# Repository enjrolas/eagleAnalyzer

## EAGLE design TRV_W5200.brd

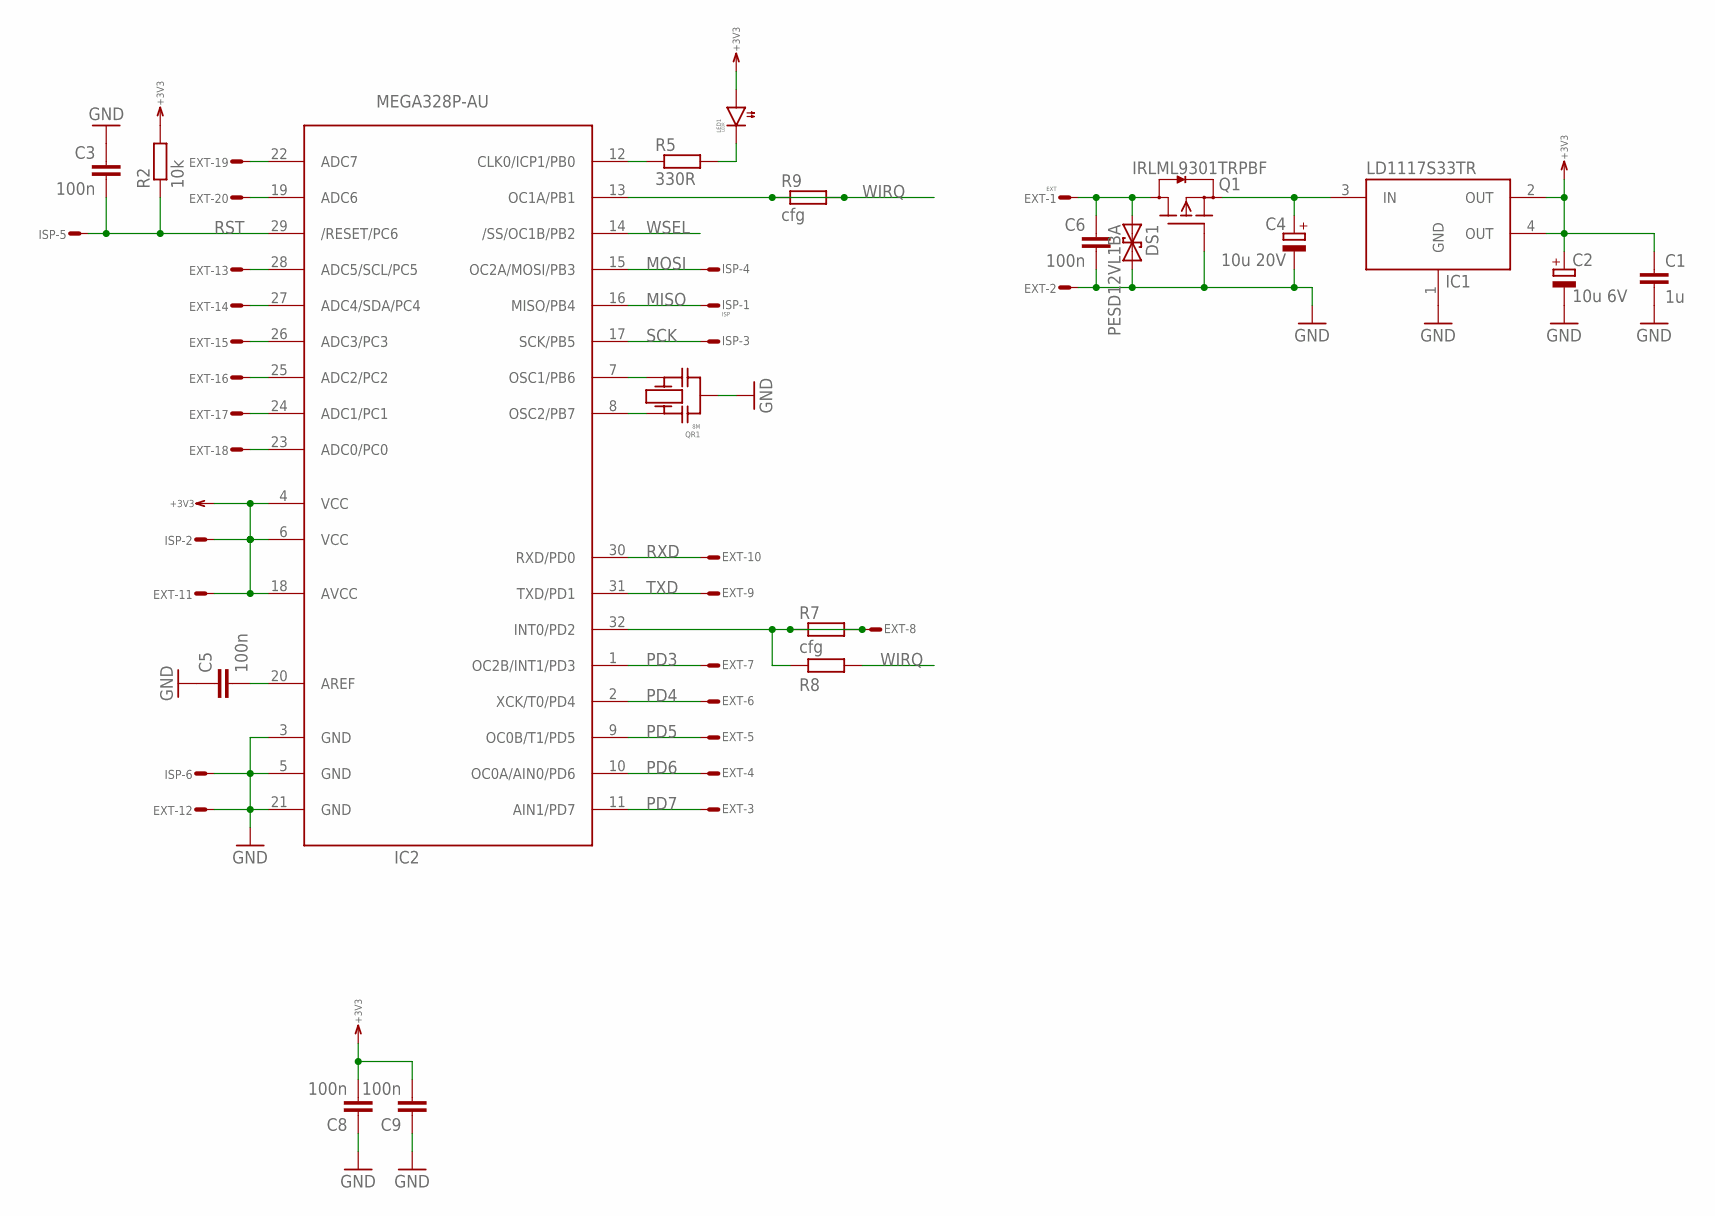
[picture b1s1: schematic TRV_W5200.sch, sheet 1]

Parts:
C1: 1u; 0603
C2: 10u 6V; SMC_A
C3, C5, C6, C8, C9: 100n; 0603
C4: 10u 20V; SMC_B
DS1: PESD12VL1BA; SOD323
EXT: EXT; ML20S
IC1: LD1117S33TR; SOT223
IC2: MEGA328P-AU; TQFP32-08
ISP: ISP; ML6S
LED1: LEDR; T1-3/4
Q1: IRLML9301TRPBF; SOT23
QR1: 8M; CSTCE
R2: 10k; 0603
R5: 330R; 0603
R7, R8, R9: cfg; 0402

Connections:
+3V3: C1.1, C2.+, C8.2, C9.2, EXT.11, IC1.2 (OUT), IC1.4 (OUT), IC2.4 (VCC), IC2.6 (VCC), IC2.18 (AVCC), ISP.2, LED1.A, R2.2; also elsewhere on the board
GND: C1.2, C2.-, C3.1, C4.-, C5.1, C6.2, C8.1, C9.1, DS1.C (2), EXT.2, EXT.12, IC1.1 (GND), IC2.3 (GND), IC2.5 (GND), IC2.21 (GND), ISP.6, Q1.1 (G), QR1.G (M); also elsewhere on the board
MISO: IC2.16 (MISO/PB4), ISP.1; also elsewhere on the board
MOSI: IC2.15 (OC2A/MOSI/PB3), ISP.4; also elsewhere on the board
unnamed: C6.1, DS1.A (1), EXT.1, Q1.3 (D)
unnamed: EXT.19, IC2.22 (ADC7)
unnamed: C4.+, IC1.3 (IN), Q1.2 (S)
unnamed: C5.2, IC2.20 (AREF)
unnamed: IC2.8 (OSC2/PB7), QR1.A (1)
unnamed: IC2.7 (OSC1/PB6), QR1.B (2)
unnamed: IC2.12 (CLK0/ICP1/PB0), R5.1
unnamed: EXT.8, IC2.32 (INT0/PD2), R7.1, R7.2, R8.1
unnamed: EXT.20, IC2.19 (ADC6)
unnamed: LED1.C, R5.2
PC0: EXT.18, IC2.23 (ADC0/PC0)
PC1: EXT.17, IC2.24 (ADC1/PC1)
PC2: EXT.16, IC2.25 (ADC2/PC2)
PC3: EXT.15, IC2.26 (ADC3/PC3)
PC4: EXT.14, IC2.27 (ADC4/SDA/PC4)
PC5: EXT.13, IC2.28 (ADC5/SCL/PC5)
PD3: EXT.7, IC2.1 (OC2B/INT1/PD3)
PD4: EXT.6, IC2.2 (XCK/T0/PD4)
PD5: EXT.5, IC2.9 (OC0B/T1/PD5)
PD6: EXT.4, IC2.10 (OC0A/AIN0/PD6)
PD7: EXT.3, IC2.11 (AIN1/PD7)
RST: C3.2, IC2.29 (/RESET/PC6), ISP.5, R2.1
RXD: EXT.10, IC2.30 (RXD/PD0)
SCK: IC2.17 (SCK/PB5), ISP.3; also elsewhere on the board
TXD: EXT.9, IC2.31 (TXD/PD1)
WIRQ: IC2.13 (OC1A/PB1), R8.2, R9.1, R9.2; also elsewhere on the board
WSEL: IC2.14 (/SS/OC1B/PB2); also elsewhere on the board

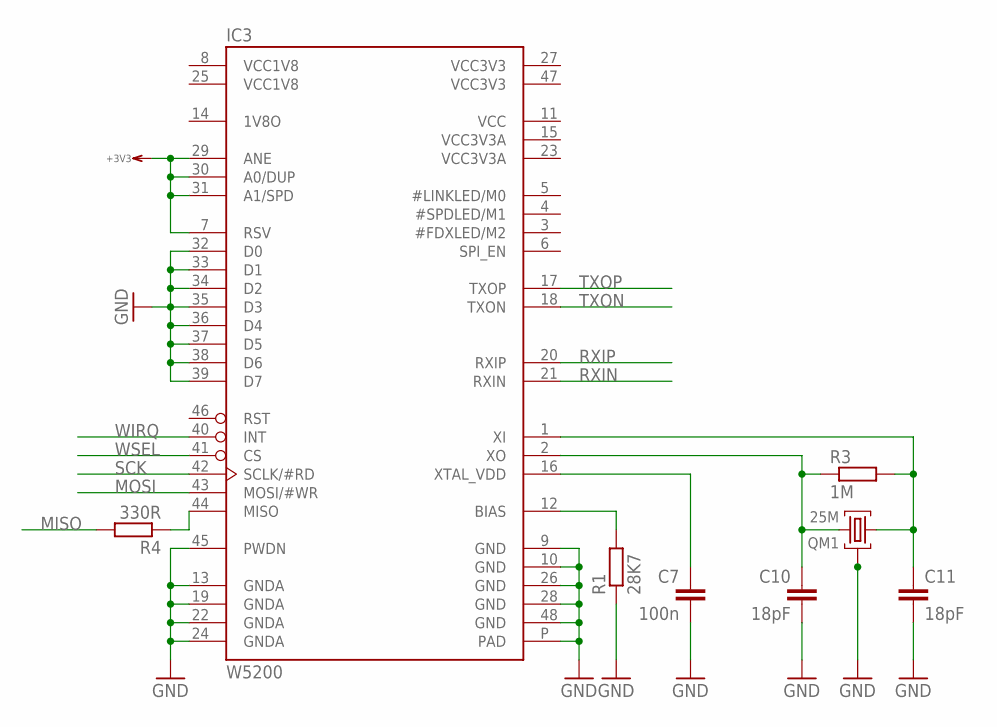
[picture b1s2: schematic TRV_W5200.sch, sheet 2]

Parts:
C7: 100n; 0603
C10, C11: 18pF; 0603
IC3: W5200; QFN48
QM1: 25M; SMD_4P_3.2X2.5
R1: 28K7; 0603
R3: 1M; 0603
R4: 330R; 0603

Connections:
+3V3: IC3.7 (RSV), IC3.29 (ANE), IC3.30 (A0/DUP), IC3.31 (A1/SPD); also elsewhere on the board
GND: C7.2, C10.2, C11.2, IC3.9 (GND), IC3.10 (GND), IC3.13 (GNDA), IC3.19 (GNDA), IC3.22 (GNDA), IC3.24 (GNDA), IC3.26 (GND), IC3.28 (GND), IC3.32 (D0), IC3.33 (D1), IC3.34 (D2), IC3.35 (D3), IC3.36 (D4), IC3.37 (D5), IC3.38 (D6), IC3.39 (D7), IC3.45 (PWDN), IC3.48 (GND), IC3.P (PAD), QM1.2 (M1), QM1.4 (M2), R1.1; also elsewhere on the board
MISO: R4.2; also elsewhere on the board
MOSI: IC3.43 (MOSI/#WR); also elsewhere on the board
unnamed: IC3.12 (BIAS), R1.2
unnamed: C7.1, IC3.16 (XTAL_VDD)
unnamed: C10.1, IC3.2 (XO), QM1.3 (2), R3.1
unnamed: C11.1, IC3.1 (XI), QM1.1, R3.2
unnamed: IC3.44 (MISO), R4.1
RXIN: IC3.21 (RXIN)
RXIP: IC3.20 (RXIP)
SCK: IC3.42 (SCLK/#RD); also elsewhere on the board
TXON: IC3.18 (TXON)
TXOP: IC3.17 (TXOP)
WIRQ: IC3.40 (INT); also elsewhere on the board
WSEL: IC3.41 (CS); also elsewhere on the board

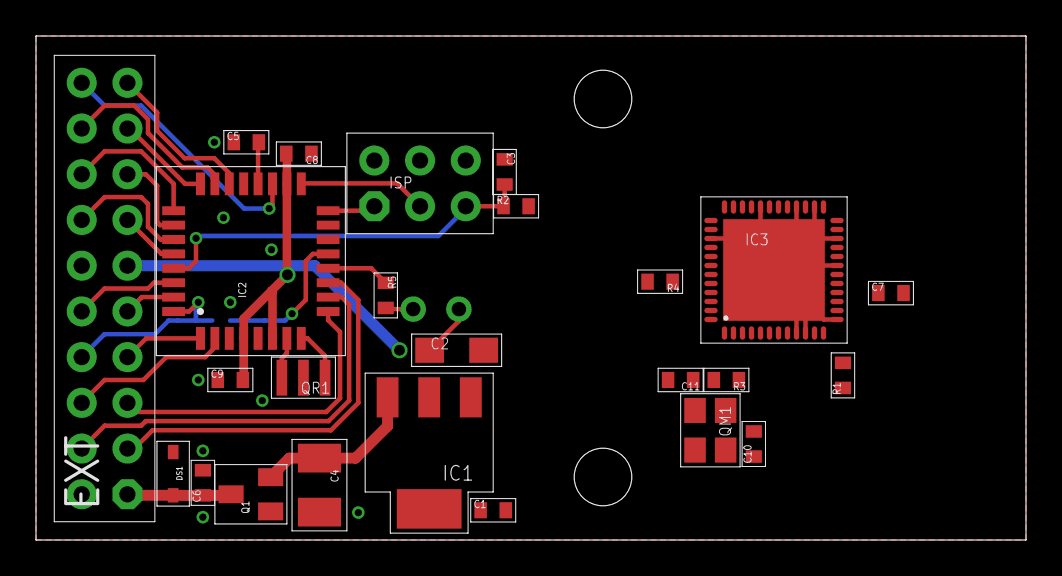
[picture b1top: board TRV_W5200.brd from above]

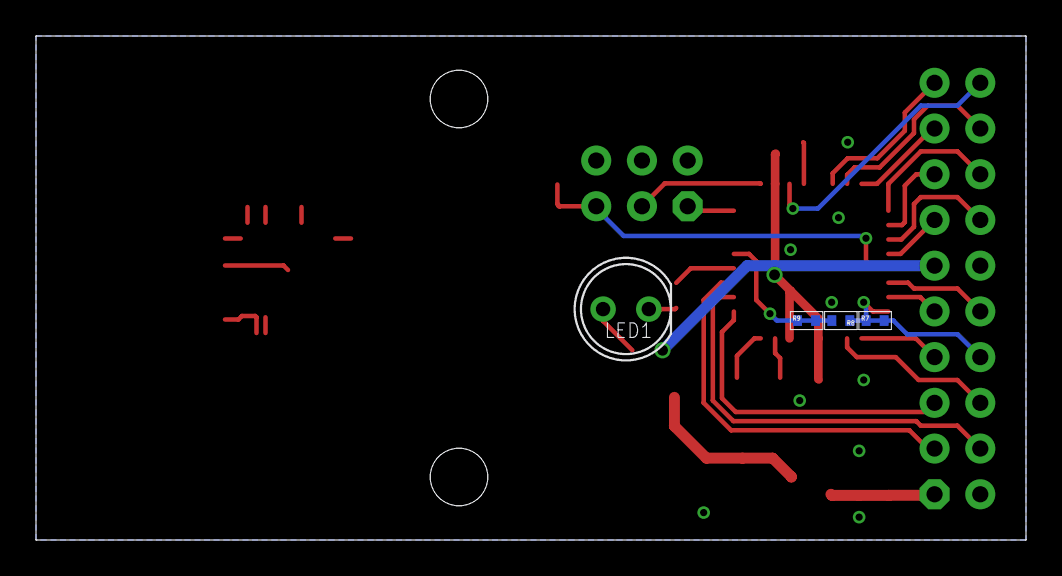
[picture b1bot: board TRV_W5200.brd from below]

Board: 2 copper layers, 55.0 x 28.0 mm, 29 parts (4 on the bottom side), 36 nets.

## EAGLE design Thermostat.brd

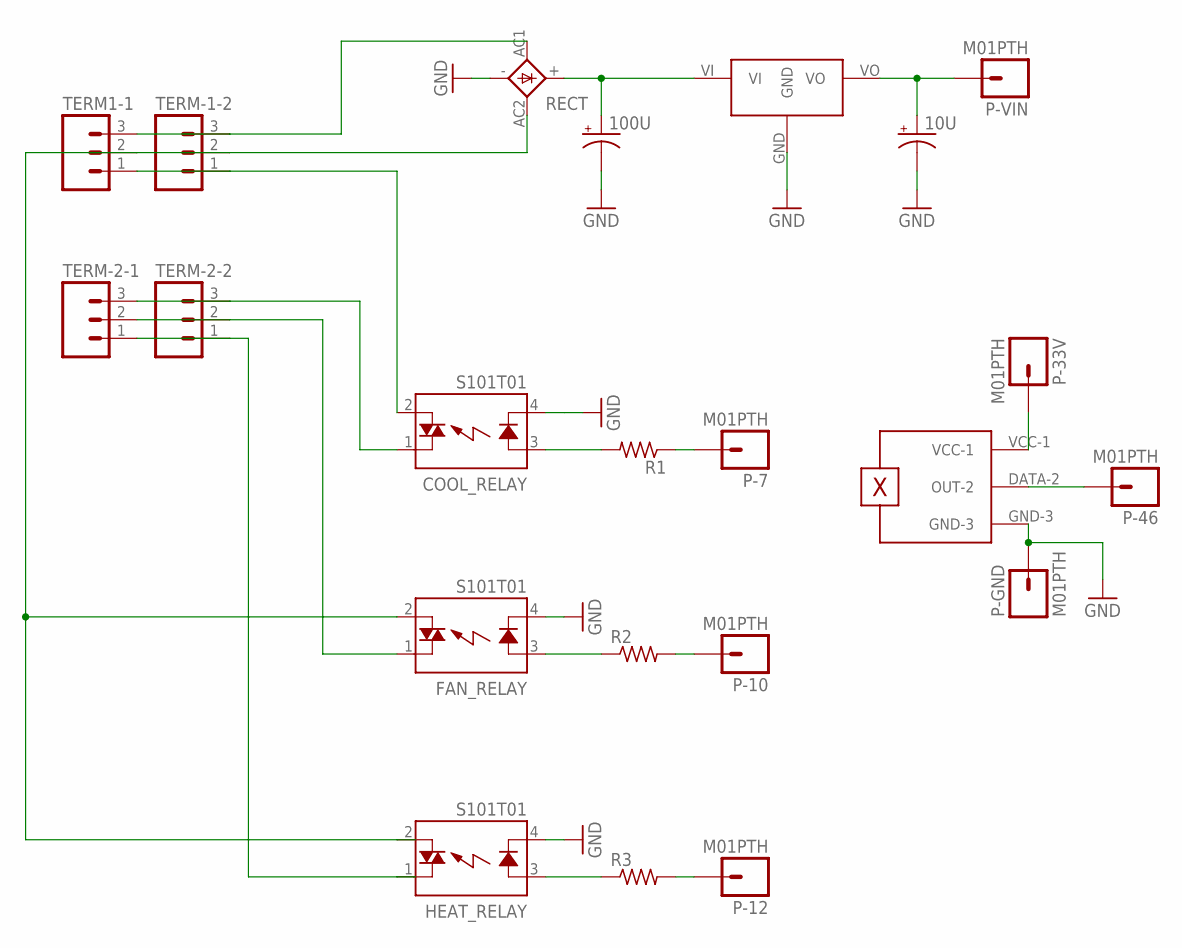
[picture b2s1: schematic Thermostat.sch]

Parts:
10U: CAP_POLPTH2; CPOL-RADIAL-10UF-25V
100U: CAP_POLPTH1; CPOL-RADIAL-100UF-25V
COOL_RELAY: S101T01; S102T0X
FAN_RELAY: S101T01; S102T0X
HEAT_RELAY: S101T01; S102T0X
P-7, P-10, P-12, P-33V, P-46: M01PTH; 1X01
P-GND: M01PTH; 1X01
P-VIN: M01PTH; 1X01
R1, R2, R3: R-US_0204/2V; 0204V
RECT: GBU4; GBU4S
TERM1-1: M031X03_NO_SILK; 1X03_NO_SILK
TERM-1-2, TERM-2-1, TERM-2-2: M031X03_NO_SILK; 1X03_NO_SILK
U$1: TMP36
U$2: V715W-500R; SWITCHINGREGULATOR

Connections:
GND: 10U.2 (-), 100U.2 (-), COOL_RELAY.4 (K), FAN_RELAY.4 (K), HEAT_RELAY.4 (K), P-GND.1, RECT.-, U$1.GND-3, U$2.GND
unnamed: COOL_RELAY.2 (DS2), TERM1-1.1, TERM-1-2.1
unnamed: HEAT_RELAY.3 (A), R3.1
unnamed: RECT.AC1 (AC2), TERM1-1.3, TERM-1-2.3
unnamed: P-7.1, R1.1
unnamed: P-46.1, U$1.DATA-2 (OUT-2)
unnamed: FAN_RELAY.3 (A), R2.1
unnamed: P-10.1, R2.2
unnamed: P-12.1, R3.2
unnamed: COOL_RELAY.3 (A), R1.2
unnamed: 10U.1 (+), P-VIN.1, U$2.VO
unnamed: P-33V.1, U$1.VCC-1
unnamed: 100U.1 (+), RECT.+, U$2.VI
unnamed: HEAT_RELAY.1 (DS1), TERM-2-1.1, TERM-2-2.1
unnamed: COOL_RELAY.1 (DS1), TERM-2-1.3, TERM-2-2.3
unnamed: FAN_RELAY.1 (DS1), TERM-2-1.2, TERM-2-2.2
P2: FAN_RELAY.2 (DS2), HEAT_RELAY.2 (DS2), RECT.AC2 (AC1), TERM1-1.2, TERM-1-2.2

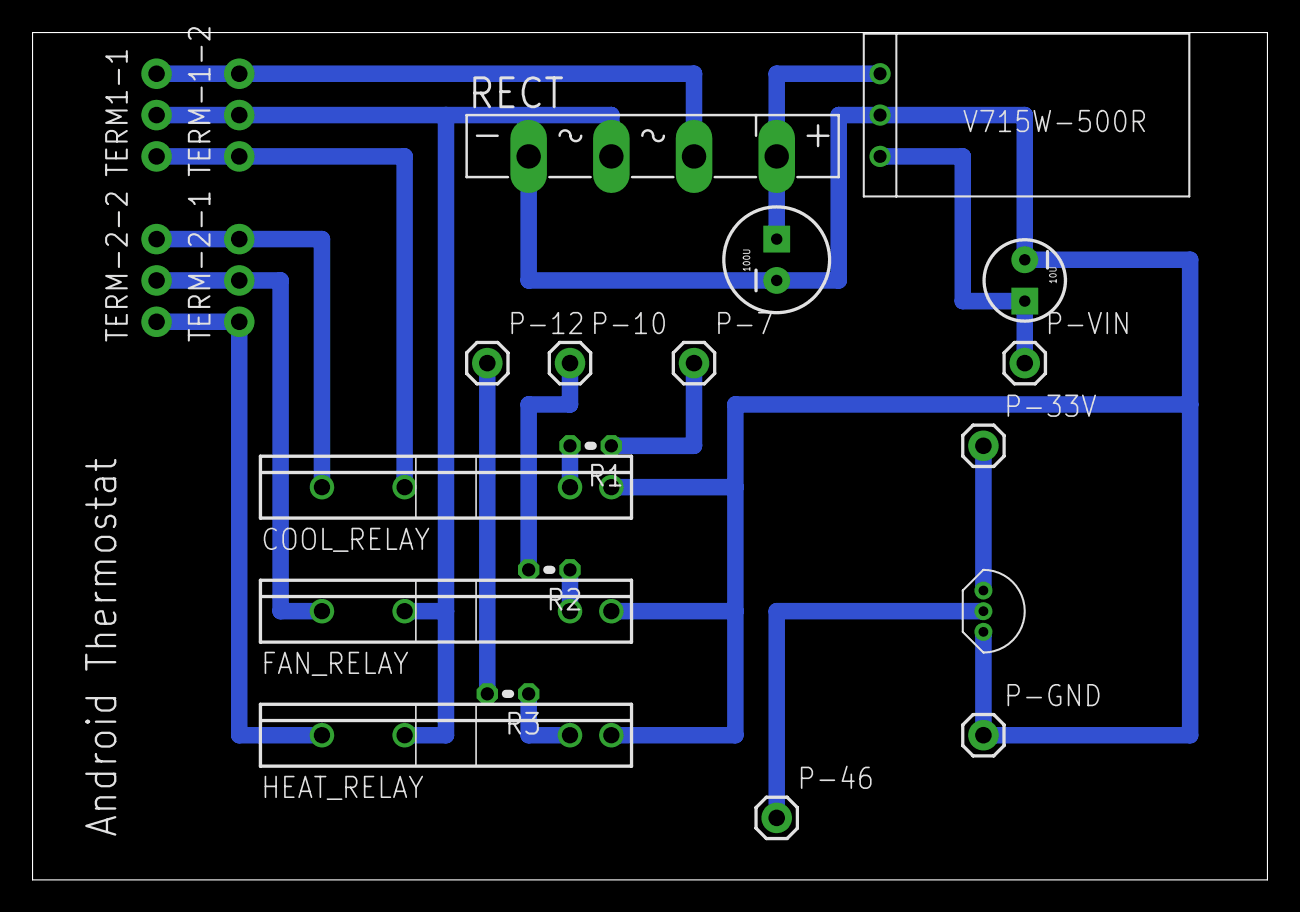
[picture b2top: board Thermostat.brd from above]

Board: 2 copper layers, 75.9 x 52.1 mm, 22 parts (0 on the bottom side), 17 nets.

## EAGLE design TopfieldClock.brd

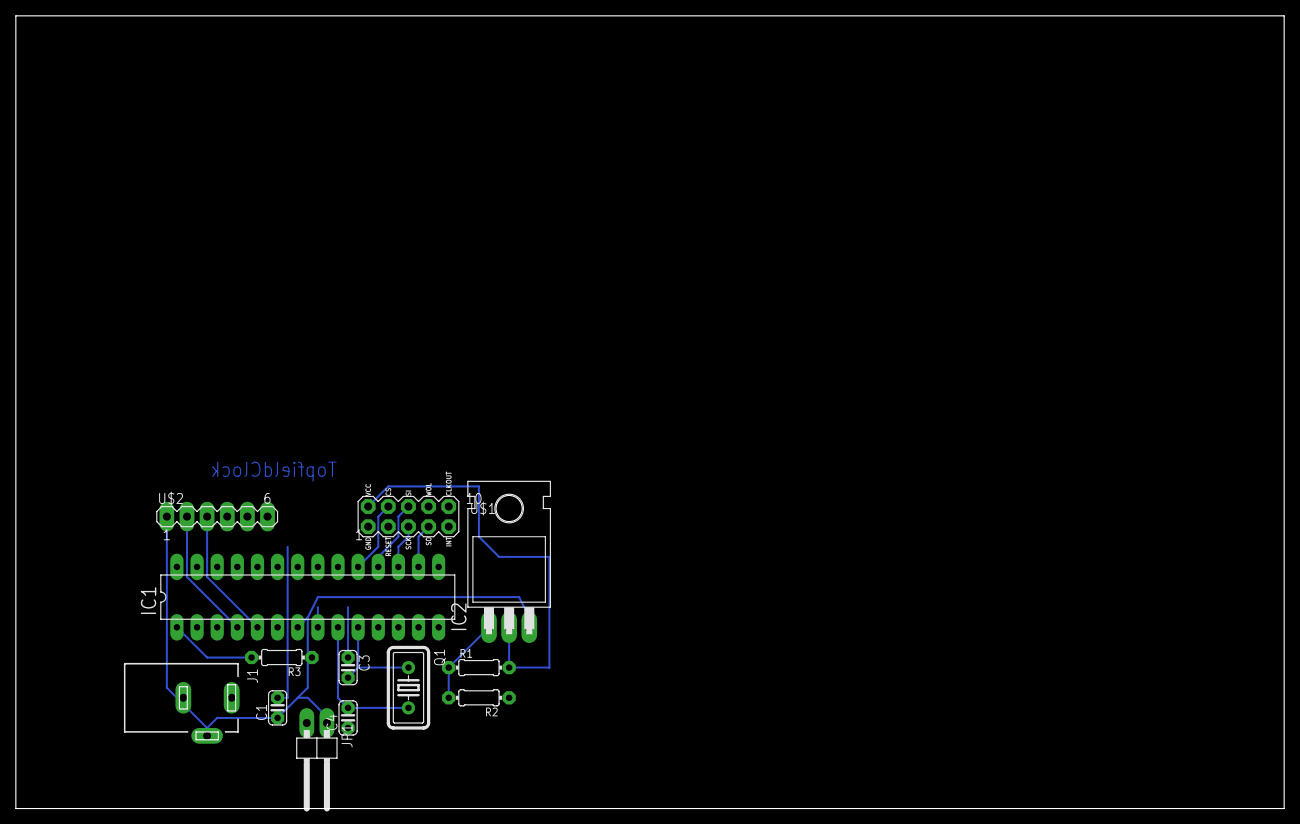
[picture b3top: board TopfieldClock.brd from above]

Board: 2 copper layers, 160.0 x 100.0 mm, 13 parts (0 on the bottom side), 13 nets.

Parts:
C1: 1u; C025-024X044
C3, C4: 22p; C025-024X044
IC1: ATMEGA168-PU; DIL28-3
IC2: 317T; TO220H
J1: DCJ0202
JP1: 1X02/90
Q1: 16M; HC18U-V
R1: 390; 0204/7
R2: 670; 0204/7
R3: 5k; 0204/7
U$1: ENC28J60MODULEENC28J60MODULECONN; ENC28J60MODULECONN
U$2: TF5000FRONTPANEL; MA06-1

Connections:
+3V3: IC2.2, R1.2, U$1.2
GND: C1.2, C3.1, C4.1, IC1.8, J1.1, JP1.2, R2.1, U$1.1, U$2.4
unnamed: IC1.4, U$2.2
unnamed: IC1.19, U$1.4
unnamed: IC1.17, U$1.5
unnamed: IC1.18, U$1.6
unnamed: IC1.5, U$2.3
unnamed: IC1.16, U$1.7
unnamed: IC2.1, R1.1, R2.2
unnamed: IC1.1, R3.2
VCC: C1.1, IC1.7, IC2.3, J1.2, J1.3, JP1.1, R3.1, U$2.1
XTAL1: C4.2, IC1.9, Q1.2
XTAL2: C3.2, IC1.10, Q1.1

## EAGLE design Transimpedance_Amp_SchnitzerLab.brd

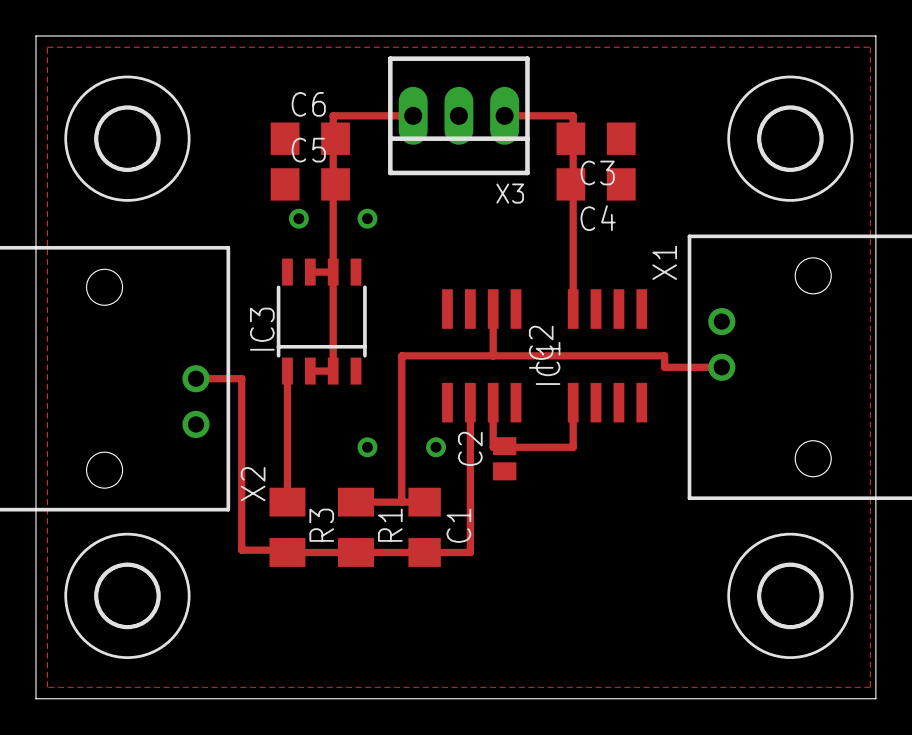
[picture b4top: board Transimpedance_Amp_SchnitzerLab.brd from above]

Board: 2 copper layers, 46.7 x 36.8 mm, 18 parts (0 on the bottom side), 7 nets.

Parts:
C1: C1206
C2: 100nf; C0504
C3, C6: 6.8uf; C1206
C4, C5: 2.2uf; C1206
IC1: SO08
IC2, IC3: SOIC8
R1, R3: M1206
U$1, U$2, U$3, U$4: 3,3
X1, X2: AMP_227161
X3: 22-23-2031

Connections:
+15V: C3.2, C4.2, IC1.8, X3.1
-5V: IC3.1, R3.1
-15V: C5.2, C6.2, IC3.2, IC3.3, IC3.6, IC3.7, X3.3
GND: C2.1, C3.1, C4.1, C5.1, C6.1, IC1.2, IC1.3, IC1.6, IC1.7, IC2.3, IC2.4, IC3.5, X1.2, X2.2, X3.2
unnamed: C1.1, IC2.2, R1.1, X1.1
unnamed: C1.2, IC2.6, R1.2, R3.2, X2.1
V+: C2.2, IC1.1, IC2.7

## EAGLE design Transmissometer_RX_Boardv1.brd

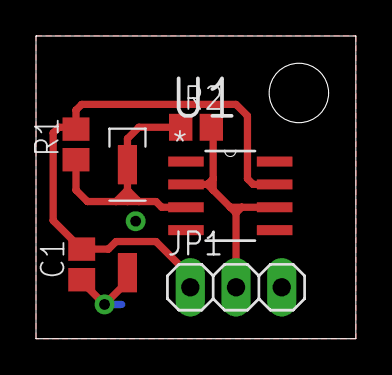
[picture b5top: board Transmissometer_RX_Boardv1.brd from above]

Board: 2 copper layers, 17.8 x 16.8 mm, 7 parts (0 on the bottom side), 4 nets.

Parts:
C1: 0.1u; C0805
JP1: 1X03
R1: 1K; R0805
R2: NP; R0805
U1: AD8628ARZ-REEL7; SOIC127P600X175-8N
U$1: TEMPT1020
U$2: STAND-OFF

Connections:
+5V: C1.2, JP1.1, R1.2, U1.7
GND: C1.1, JP1.3, U1.4, U$1.P$1
unnamed: R1.1, R2.1, U1.3, U$1.P$2
OUT: JP1.2, R2.2, U1.2, U1.6

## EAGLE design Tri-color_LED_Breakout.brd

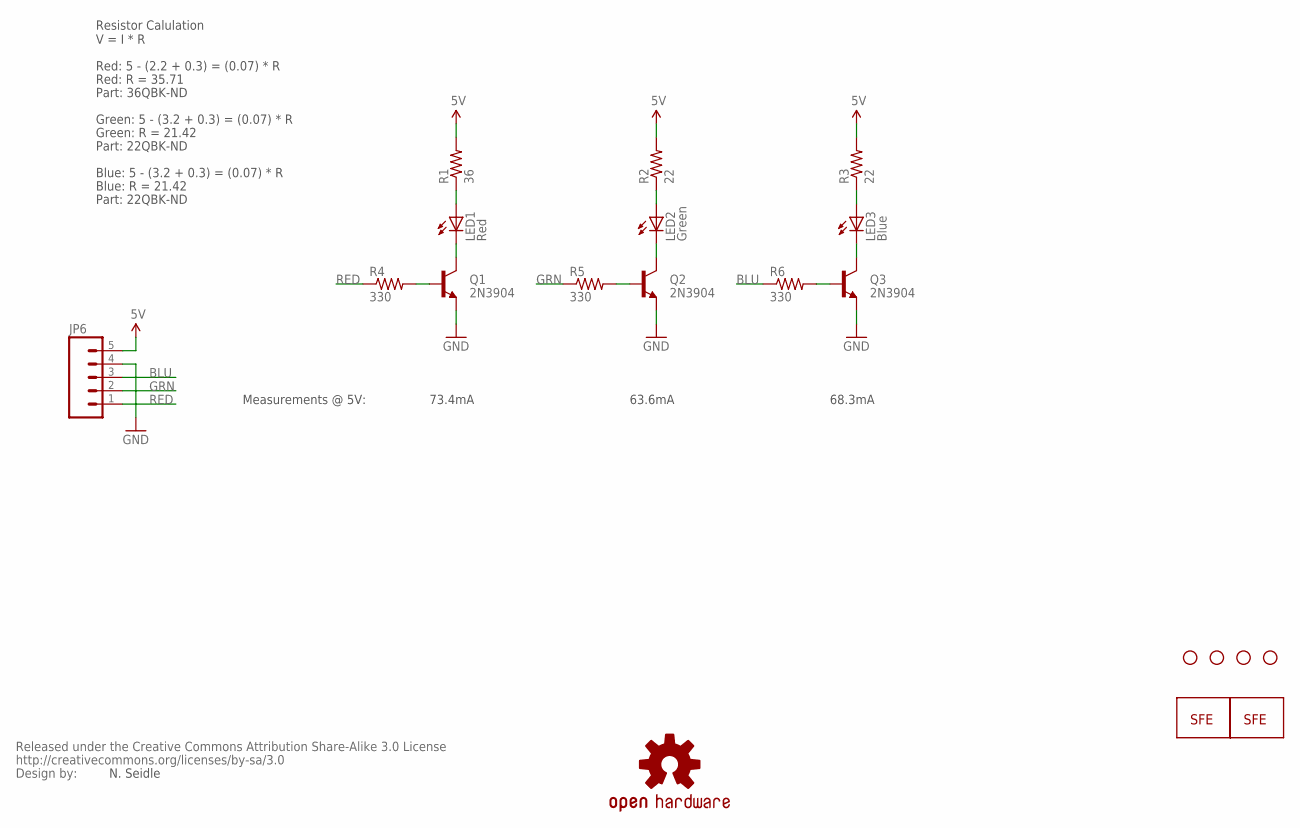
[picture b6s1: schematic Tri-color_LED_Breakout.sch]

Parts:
JP1, JP2, JP3, JP4: STAND-OFF
JP5, JP7: LOGO-SFESK; SFE-LOGO-FLAME
JP6: M05PTH; 1X05
LED1: Red; LED10MM
LED2: Green; LED10MM
LED3: Blue; LED10MM
Q1, Q2, Q3: 2N3904; TO-92
R1: 36; AXIAL-0.4
R2, R3: 22; AXIAL-0.4
R4, R5, R6: 330; AXIAL-0.3
U$1: CREATIVE_COMMONS
U$6: OSHW-LOGOS; OSHW-LOGO-S

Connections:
5V: JP6.5, R1.P$2 (2), R2.P$2 (2), R3.P$2 (2)
BLU: JP6.3, R6.P$1 (1)
GND: JP6.4, Q1.1 (E), Q2.1 (E), Q3.1 (E)
GRN: JP6.2, R5.P$1 (1)
unnamed: LED2.A, R2.P$1 (1)
unnamed: LED3.A, R3.P$1 (1)
unnamed: LED1.A, R1.P$1 (1)
unnamed: LED1.C, Q1.3 (C)
unnamed: LED2.C, Q2.3 (C)
unnamed: LED3.C, Q3.3 (C)
unnamed: Q1.2 (B), R4.P$2 (2)
unnamed: Q2.2 (B), R5.P$2 (2)
unnamed: Q3.2 (B), R6.P$2 (2)
RED: JP6.1, R4.P$1 (1)

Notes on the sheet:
N. Seidle
Resistor Calulation V = I * R
Red: 5 - (2.2 + 0.3) = (0.07) * R
Red: R = 35.71
Green: 5 - (3.2 + 0.3) = (0.07) * R
Green: R = 21.42
Blue: 5 - (3.2 + 0.3) = (0.07) * R
Blue: R = 21.42
Part: 36QBK-ND
Part: 22QBK-ND
Measurements @ 5V:
73.4mA
63.6mA
68.3mA

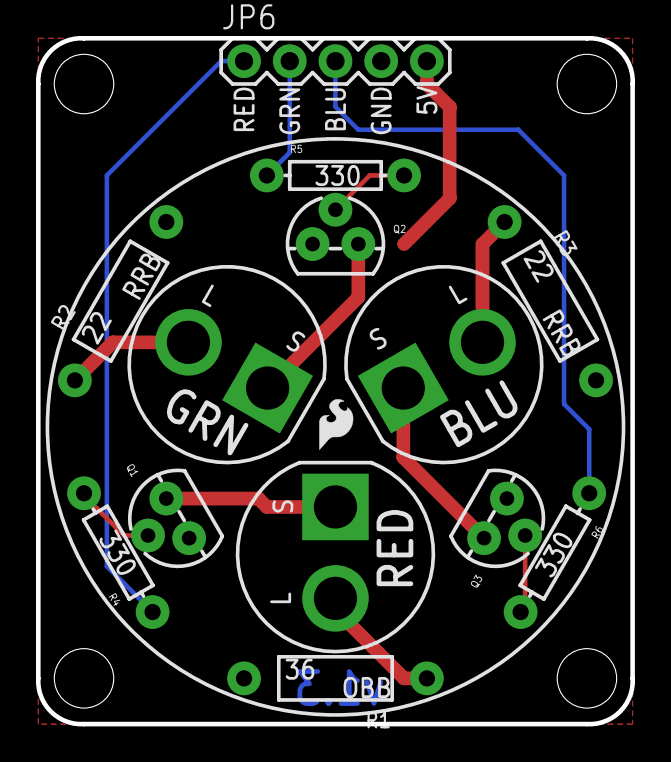
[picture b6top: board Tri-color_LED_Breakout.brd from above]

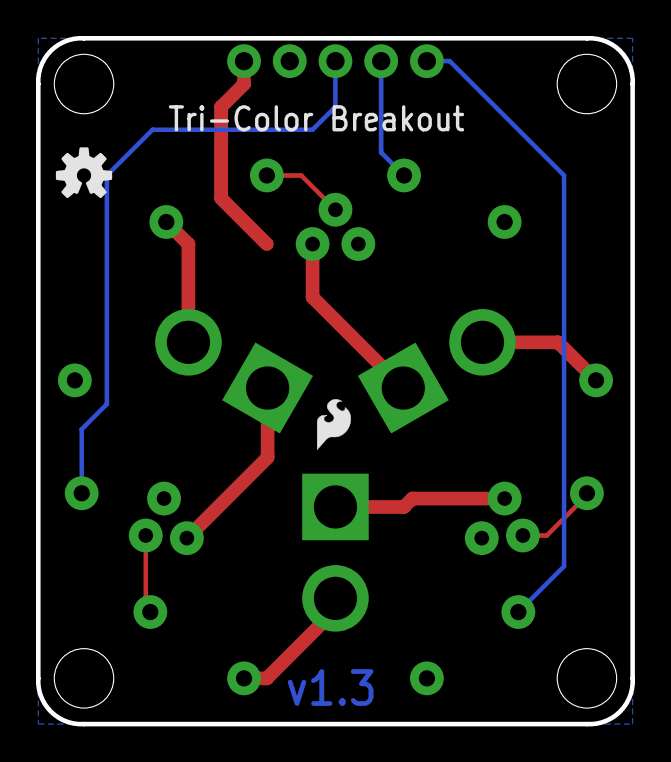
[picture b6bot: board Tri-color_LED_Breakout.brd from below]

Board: 2 copper layers, 33.0 x 38.1 mm, 21 parts (2 on the bottom side), 14 nets.

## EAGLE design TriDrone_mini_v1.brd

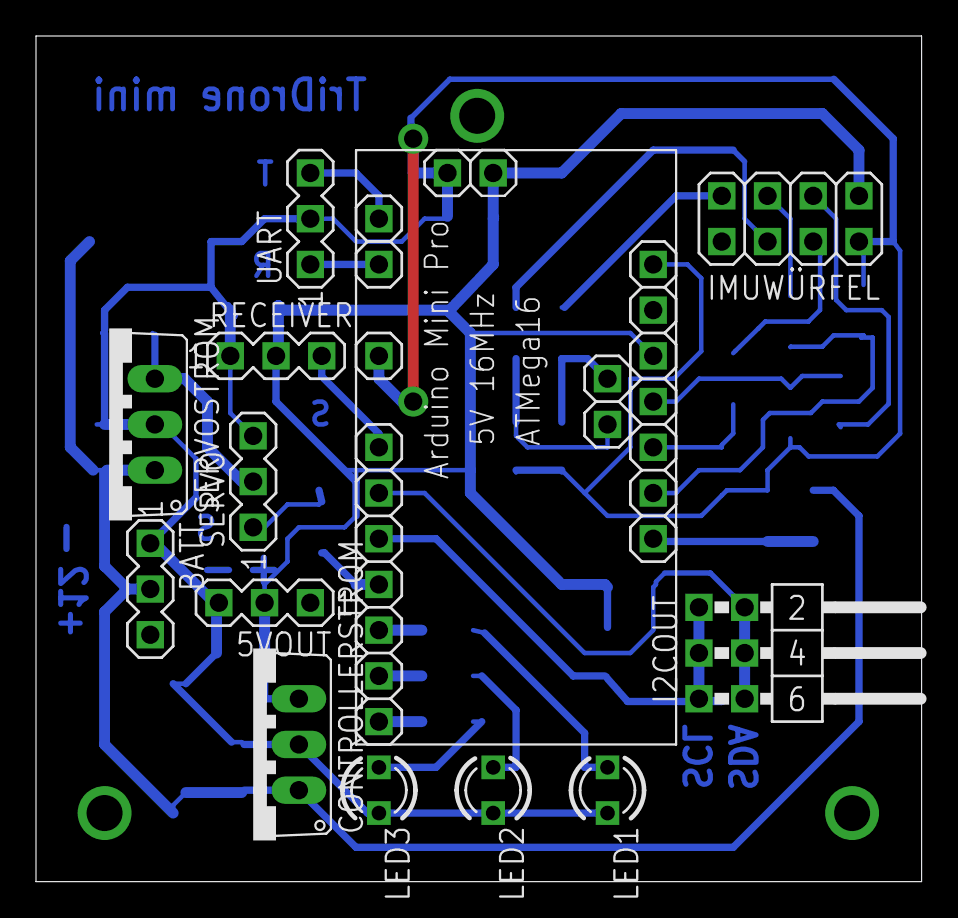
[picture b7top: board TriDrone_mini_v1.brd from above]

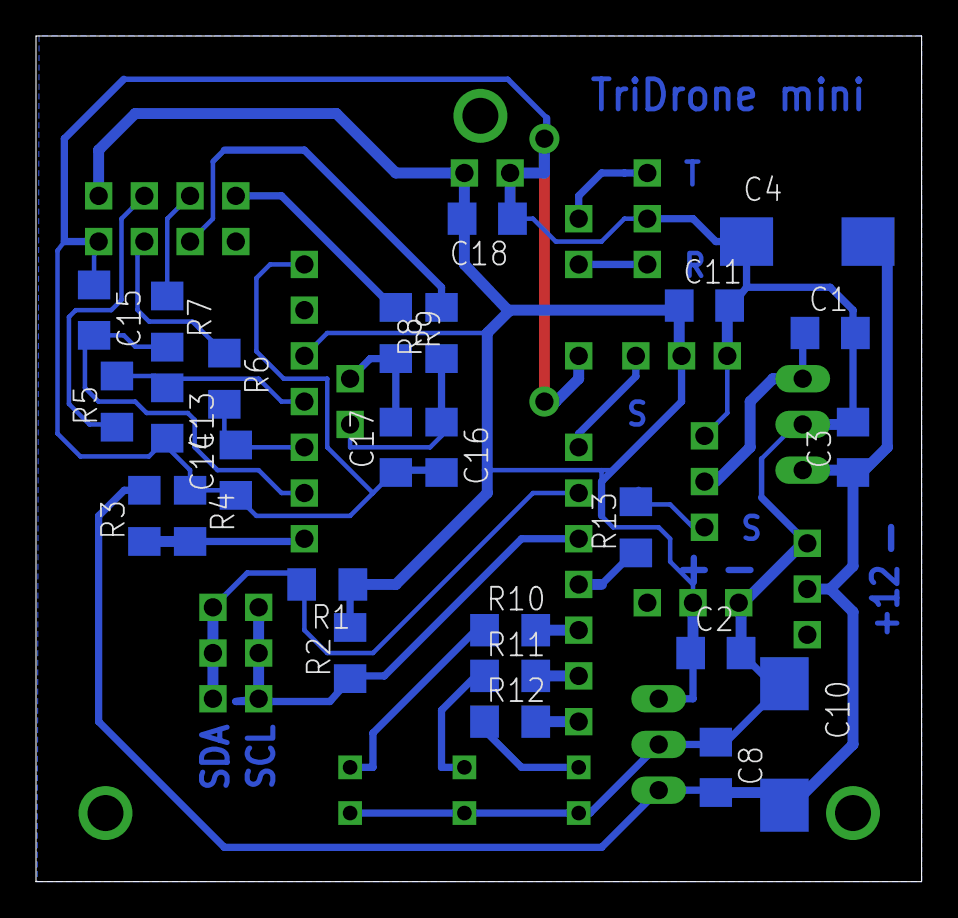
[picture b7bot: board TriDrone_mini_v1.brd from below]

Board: 2 copper layers, 49.2 x 47.0 mm, 39 parts (26 on the bottom side), 28 nets.

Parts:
5VOUT: MA03-2W; MA03-1
BATT: lipo 12.6V; MA03-1
C1, C2, C3, C8, C11, C13, C14, C15, C18: 100nF; C1206
C4, C10: 100µF; D/7343-31W
C16, C17: 1µF; C1206
CONTROLLERSTROM: 7805TV; TO220V
I2COUT: 6pin; MA07-2W
IMUWÜRFEL: 8pin; 2X04
LED1, LED2, LED3: blue; LED3MM
R1, R2, R8, R9: 10k; R1206
R3: 51k; R1206
R4: 33k; R1206
R5, R6, R7: 36k; R1206
R10, R11, R12: 330; R1206
R13: 3.3k; R1206
RECEIVER: MA03-2W; MA03-1
SERVO: MA03-2W; MA03-1
SERVOSTROM: 7805TV; TO220V
U$1: ARDUINOMINIPRO; 1X12
UART: MA03-2W; MA03-1

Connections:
+12V: BATT.2, C3.1, C4.+, C8.2, C10.+, CONTROLLERSTROM.1, R3.2, SERVOSTROM.1
ACCX: C16.1, R8.1, U$1.A4
ACCY: C17.2, R9.2, U$1.A5
GND: 5VOUT.3, BATT.1, C1.2, C2.2, C3.2, C4.-, C8.1, C10.-, C11.2, C13.2, C14.1, C15.1, C16.2, C17.1, C18.1, CONTROLLERSTROM.2, IMUWÜRFEL.2, LED1.K, LED2.K, LED3.K, R4.1, RECEIVER.1, SERVO.3, SERVOSTROM.2, U$1.GND, U$1.GND2, U$1.GND3, UART.2
GYRONICK: C14.2, R6.2, U$1.A2
GYROROLL: C13.1, R5.2, U$1.A3
GYROYAW: C15.2, R7.2, U$1.A1
LED1: R10.2, U$1.7
LED2: R11.2, U$1.8
LED3: R12.2, U$1.9
unnamed: LED1.A, R10.1
unnamed: LED2.A, R11.1
unnamed: IMUWÜRFEL.3, R5.1
unnamed: C1.1, SERVO.2, SERVOSTROM.3
unnamed: LED3.A, R12.1
unnamed: R13.2, SERVO.1
unnamed: R3.1, R4.2, U$1.A0
unnamed: IMUWÜRFEL.4, R6.1
unnamed: IMUWÜRFEL.5, R7.1
unnamed: IMUWÜRFEL.6, R8.2
unnamed: IMUWÜRFEL.7, R9.1
REC: RECEIVER.3, U$1.3
RXD: U$1.RXI2, UART.1
SCL: I2COUT.1, I2COUT.3, I2COUT.5, R2.1, U$1.5
SDA: I2COUT.2, I2COUT.4, I2COUT.6, R1.2, U$1.4
SERVO: R13.1, U$1.6
TXD: U$1.TXO2, UART.3
VCC: 5VOUT.2, C2.1, C11.1, C18.2, CONTROLLERSTROM.3, IMUWÜRFEL.1, R1.1, R2.2, RECEIVER.2, U$1.VCC, U$1.VCC2

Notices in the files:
parts and their libraries:
SparkFun-Connectors: Licensing: CC v3.0 Share-Alike You are welcome to use this library for commercial purposes.
SparkFun: Released under the Creative Commons Attribution Share-Alike 3.0 License
SparkFun: http://creativecommons.org/licenses/by-sa/3.0
